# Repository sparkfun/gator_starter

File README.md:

SparkFun gator:starter Protosnap
========================================

[*SparkFun gator:starter - SEN-14891*](https://www.sparkfun.com/products/14891)

The gator:starter breaks out a temperature sensor, light sensor, and RGB LED into an alligator clippable format for use with micro:bit as well as the gator:bit expansion for micro:bit.

Repository Contents
-------------------

* **/Firmware** - Example code used with the gator:starter. While they are compiled HEX codes, you can modify the example code once they are imported into MakeCode editor.
* **/Hardware** - Eagle design files (.brd, .sch)
* **/Production** - Production panel files (.brd)

Documentation
--------------
* **[Library](https://github.com/sparkfun/pxt-gator-temp) - PXT temperature sensor firmware
* **[Hookup Guide](https://learn.sparkfun.com/tutorials/gatorstarter-protosnap-hookup-guide)** - Basic hookup guide for the gator:starter.

Product Versions
----------------
* [SEN-14891](https://www.sparkfun.com/products/14891)- The gator:starter contains a few gator-clippable sensors (Temperature and Light) along with an RGB LED

License Information
-------------------

This product is _**open source**_! 

Please review the LICENSE.md file for license information. 

If you have any questions or concerns on licensing, please contact techsupport@sparkfun.com.

Distributed as-is; no warranty is given.

- Your friends at SparkFun.

_<COLLABORATION CREDIT>_

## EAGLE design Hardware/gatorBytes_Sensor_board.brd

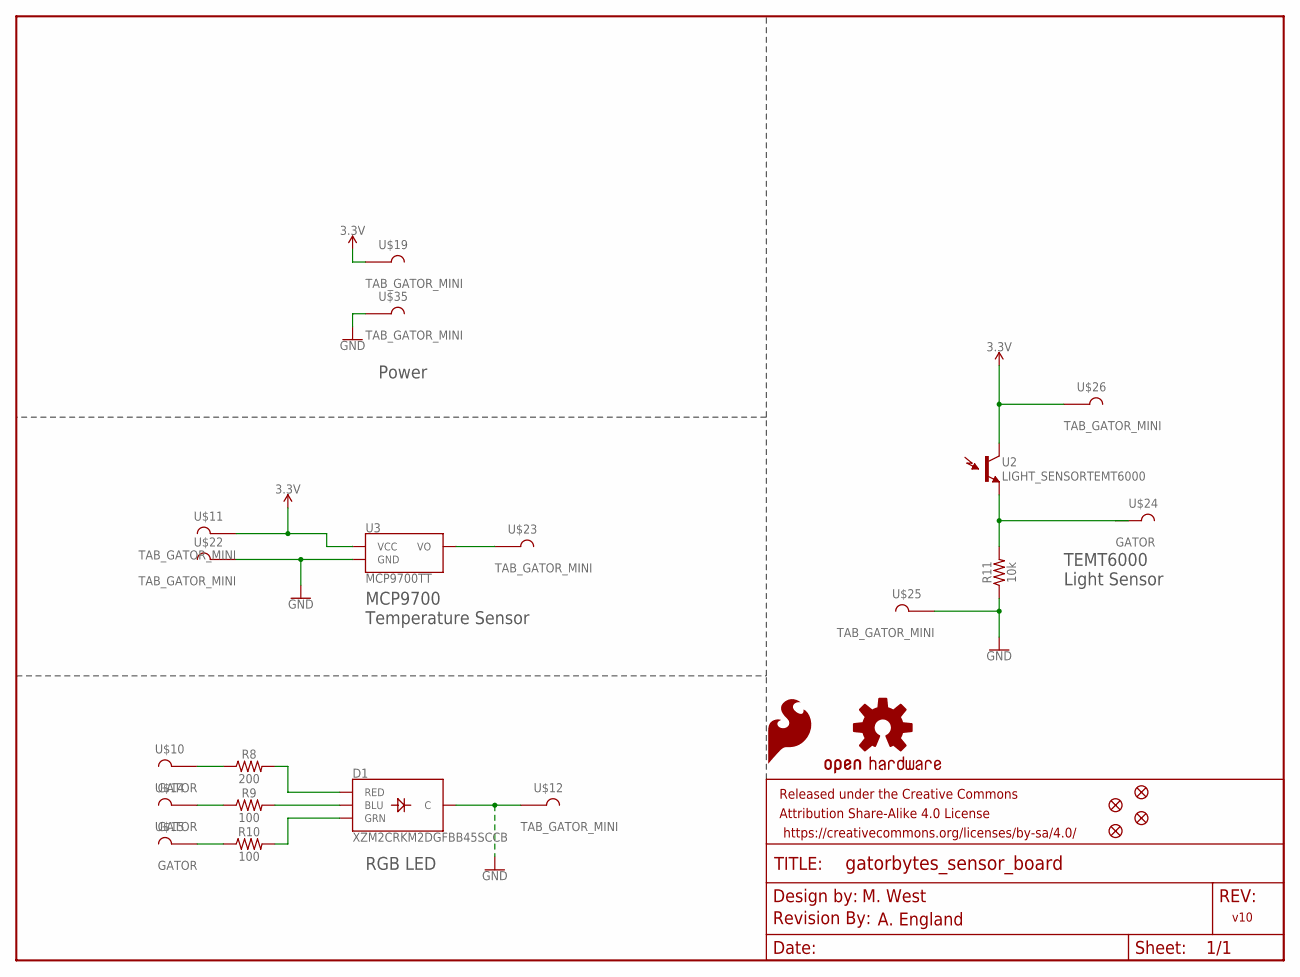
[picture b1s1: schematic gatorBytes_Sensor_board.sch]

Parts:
D1: XZM2CRKM2DGFBB45SCCB; PLCC4SMDLED
FD1, FD2, FD3, FD4: FIDUCIALUFIDUCIAL; FIDUCIAL-MICRO
FRAME1: FRAME-LETTER; CREATIVE_COMMONS
LOGO1: SFE_LOGO_FLAME.1_INCH; SFE_LOGO_FLAME_.1
LOGO2: OSHW-LOGOS; OSHW-LOGO-S
LOGO7: REVISION
R8: 200; 0603
R9, R10: 100; 0603
R11: 10k; 0603
U2: LIGHT_SENSORTEMT6000; TEMT6000
U3: MCP9700TT; SOT23-3
U$10, U$14, U$15, U$24: GATOR
U$11, U$12, U$19, U$22, U$23, U$25, U$26, U$35: TAB_GATOR_MINI

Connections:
3.3V: U2.COLLECTOR (C1), U3.1 (VCC), U$11.P1, U$19.P1, U$26.P1
GND: D1.4 (C), R11.1, U3.3 (GND), U$12.P1, U$22.P1, U$25.P1, U$35.P1
unnamed: U3.2 (VO), U$23.P1
unnamed: D1.3 (BLU), R9.2
unnamed: D1.1 (RED), R8.2
unnamed: D1.2 (GRN), R10.2
unnamed: R8.1, U$10.P$1, U$10.P$2
unnamed: R9.1, U$14.P$1, U$14.P$2
unnamed: R10.1, U$15.P$1, U$15.P$2
unnamed: R11.2, U2.EMITTER (E1), U$24.P$1, U$24.P$2

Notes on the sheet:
RGB LED
MCP9700 Temperature Sensor
TEMT6000 Light Sensor
M. West
v10
Power
A. England

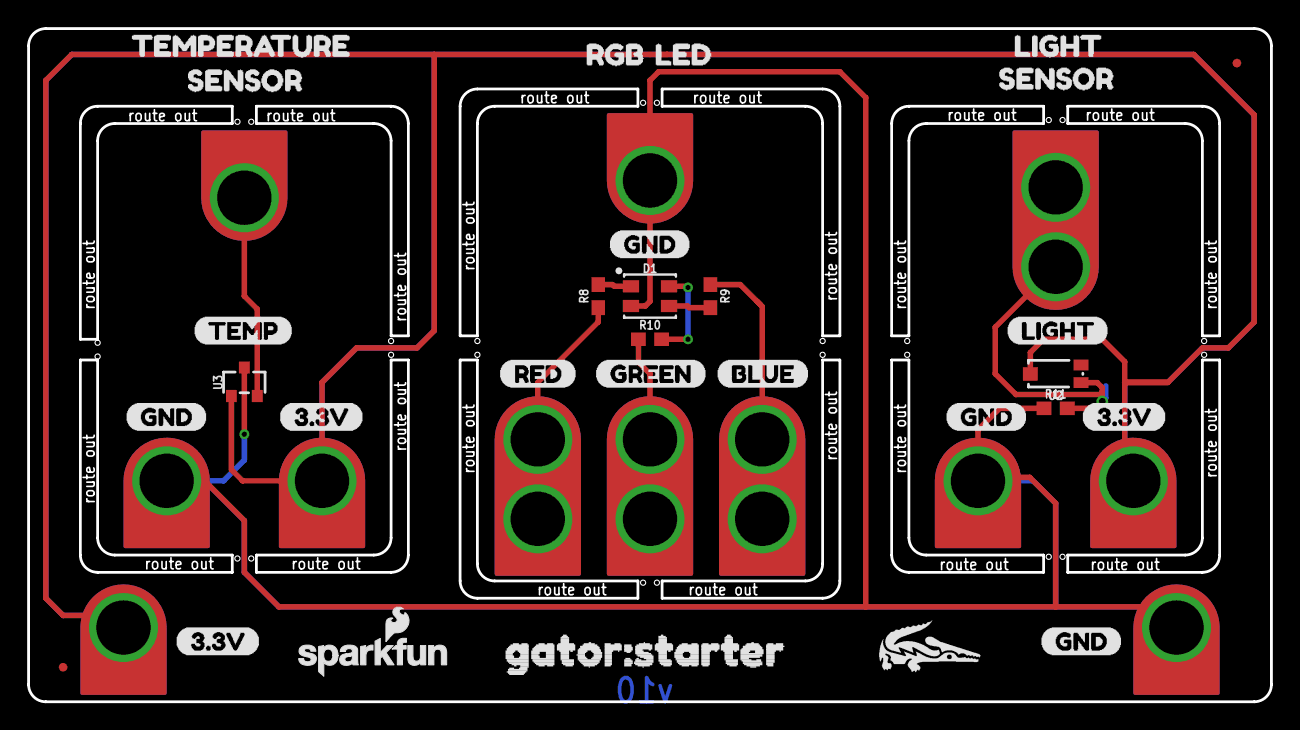
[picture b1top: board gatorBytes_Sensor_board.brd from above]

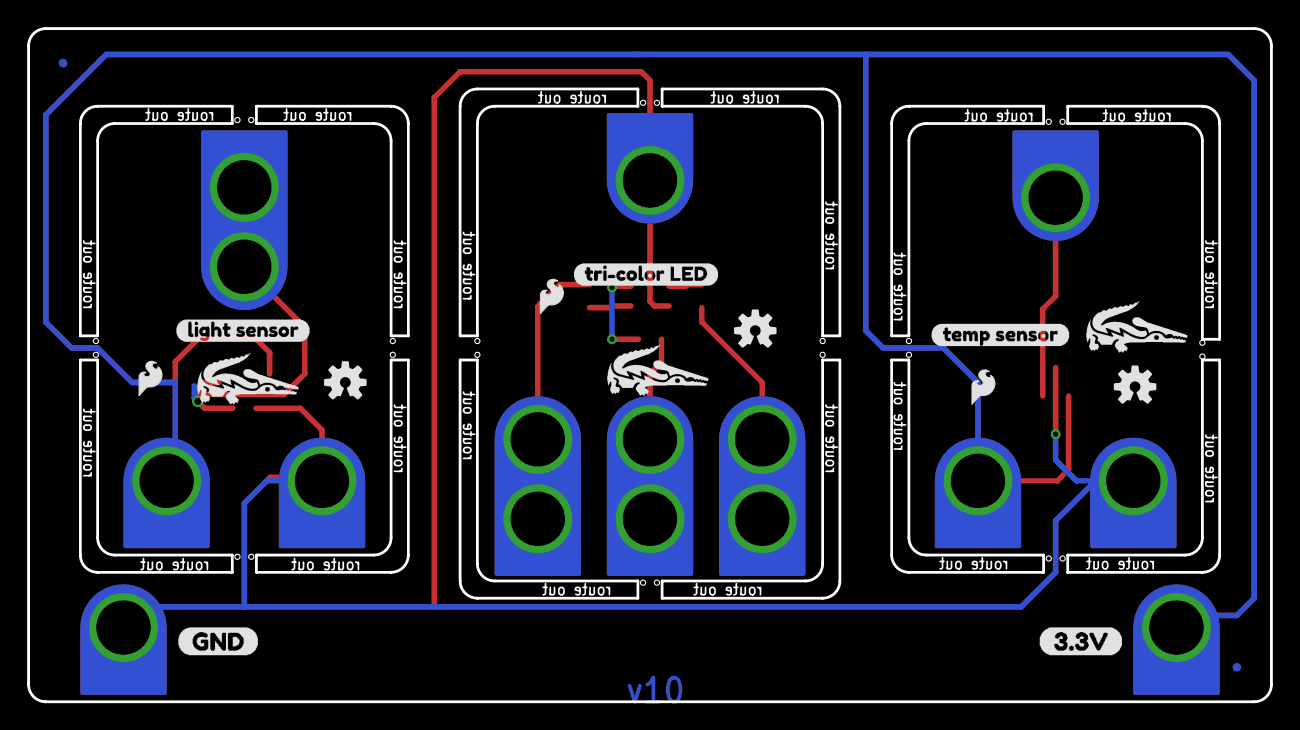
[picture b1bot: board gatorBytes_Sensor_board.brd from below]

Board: 2 copper layers, 91.4 x 49.5 mm, 61 parts (16 on the bottom side), 10 nets.

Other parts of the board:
LOGO3, LOGO5: OSHW-LOGOS; OSHW-LOGO-S
LOGO4, LOGO6: SFE_LOGO_FLAME.1_INCH; SFE_LOGO_FLAME_.1
U$1, U$6, U$7, U$38, U$39: GND0
U$2, U$3, U$36, U$37: 3#3V1
U$4: BLUE10
U$5: SFE_LOGO_NAME_FLAME_.1
U$8: GREEN9
U$9, U$20: LIGHT4
U$13: TEMP3
U$16, U$21: SENSOR2
U$17: TEMPERATURE3
U$18: RED8
U$27: LED5
U$28, U$29, U$41, U$70: GATOR#PNG
U$30: GATOR#STARTER0
U$31: LIGHT_SENSOR0
U$32: TEMP_SENSOR3
U$33: ORDERING_INSTRUCTIONS
U$34: TRI#COLOR_LED1
U$40: RGB0

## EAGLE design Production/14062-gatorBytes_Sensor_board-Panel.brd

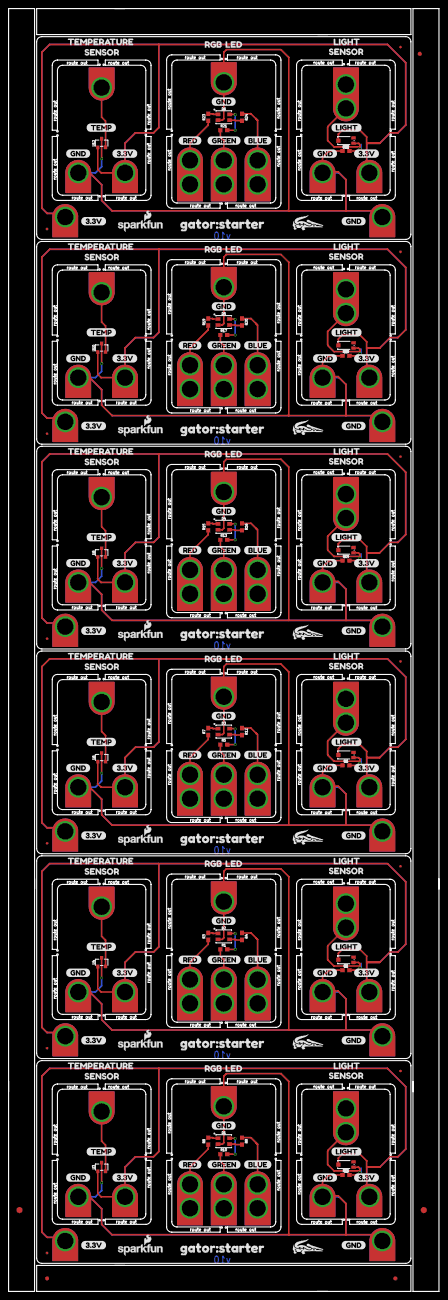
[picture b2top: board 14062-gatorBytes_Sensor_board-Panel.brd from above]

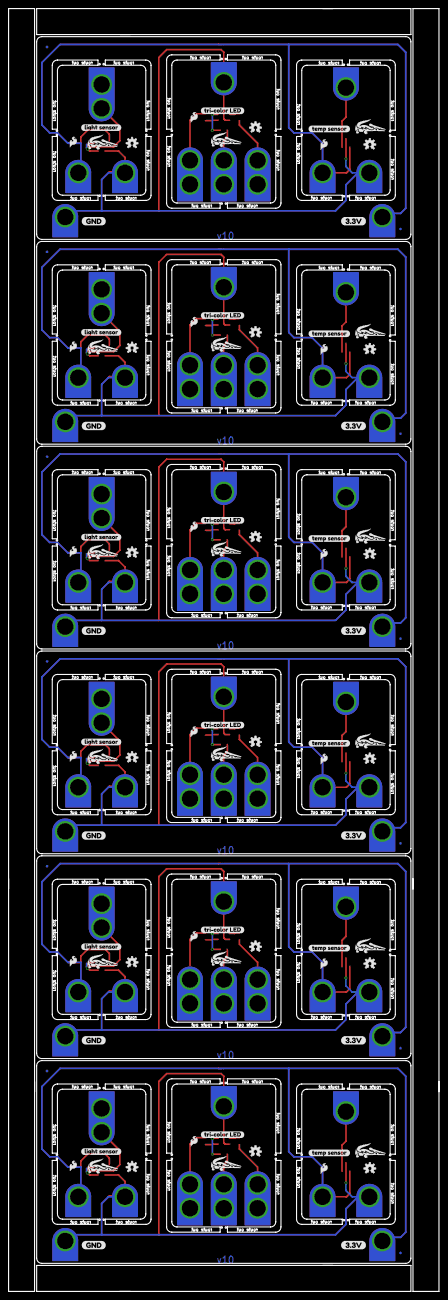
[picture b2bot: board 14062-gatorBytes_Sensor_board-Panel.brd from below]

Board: 2 copper layers, 105.2 x 313.4 mm, 353 parts (96 on the bottom side), 60 nets.

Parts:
D1, D2, D3, D4, D5, D6: XZM2CRKM2DGFBB45SCCB; PLCC4SMDLED
E$1, E$5, E$6: FIDUCIAL-1X2
E$3, E$4: FIDUCIAL-1.5X3
FD1, FD2, FD3, FD4, FD5, FD6, FD7, FD8, FD9, FD10, FD11, FD12, FD13, FD14, FD15, FD16, FD17, FD18, FD19, FD20, FD21, FD22, FD23, FD24: FIDUCIALUFIDUCIAL; FIDUCIAL-MICRO
LOGO1, LOGO4, LOGO6, LOGO7, LOGO10, LOGO12, LOGO13, LOGO16, LOGO18, LOGO19, LOGO22, LOGO24, LOGO25, LOGO28, LOGO30, LOGO31, LOGO34, LOGO36: SFE_LOGO_FLAME.1_INCH; SFE_LOGO_FLAME_.1
LOGO2, LOGO3, LOGO5, LOGO8, LOGO9, LOGO11, LOGO14, LOGO15, LOGO17, LOGO20, LOGO21, LOGO23, LOGO26, LOGO27, LOGO29, LOGO32, LOGO33, LOGO35: OSHW-LOGOS; OSHW-LOGO-S
R1, R4, R5, R9, R10, R12, R13, R16, R17, R20, R21, R24: 100; 0603
R2, R6, R11, R14, R18, R22: 10k; 0603
R3, R7, R8, R15, R19, R23: 200; 0603
U1, U2, U5, U7, U9, U11: LIGHT_SENSORTEMT6000; TEMT6000
U3, U4, U6, U8, U10, U12: MCP9700TT; SOT23-3
U$1, U$6, U$7, U$38, U$39, U$54, U$55, U$77, U$78, U$82, U$96, U$97, U$118, U$119, U$123, U$137, U$138, U$159, U$160, U$164, U$178, U$179, U$200, U$201, U$205, U$219, U$220, U$241, U$242, U$246: GND0
U$2, U$3, U$36, U$37, U$51, U$52, U$75, U$76, U$93, U$94, U$116, U$117, U$134, U$135, U$157, U$158, U$175, U$176, U$198, U$199, U$216, U$217, U$239, U$240: 3#3V1
U$4, U$53, U$95, U$136, U$177, U$218: BLUE10
U$5, U$72, U$113, U$154, U$195, U$236: SFE_LOGO_NAME_FLAME_.1
U$8, U$56, U$98, U$139, U$180, U$221: GREEN9
U$9, U$20, U$57, U$62, U$99, U$104, U$140, U$145, U$181, U$186, U$222, U$227: LIGHT4
U$10, U$14, U$15, U$24, U$33, U$44, U$45, U$48, U$83, U$86, U$87, U$90, U$124, U$127, U$128, U$131, U$165, U$168, U$169, U$172, U$206, U$209, U$210, U$213: GATOR
U$11, U$12, U$19, U$22, U$23, U$25, U$26, U$35, U$42, U$43, U$46, U$47, U$49, U$50, U$73, U$74, U$84, U$85, U$88, U$89, U$91, U$92, U$114, U$115, U$125, U$126, U$129, U$130, U$132, U$133, U$155, U$156, U$166, U$167, U$170, U$171, U$173, U$174, U$196, U$197, U$207, U$208, U$211, U$212, U$214, U$215, U$237, U$238: TAB_GATOR_MINI
U$13, U$58, U$100, U$141, U$182, U$223: TEMP3
U$16, U$21, U$61, U$63, U$103, U$105, U$144, U$146, U$185, U$187, U$226, U$228: SENSOR2
U$17, U$60, U$102, U$143, U$184, U$225: TEMPERATURE3
U$18, U$59, U$101, U$142, U$183, U$224: RED8
U$27, U$64, U$106, U$147, U$188, U$229: LED5
U$28, U$29, U$41, U$65, U$66, U$67, U$70, U$80, U$107, U$108, U$109, U$121, U$148, U$149, U$150, U$162, U$189, U$190, U$191, U$203, U$230, U$231, U$232, U$244: GATOR#PNG
U$30, U$81, U$122, U$163, U$204, U$245: GATOR#STARTER0
U$31, U$68, U$110, U$151, U$192, U$233: LIGHT_SENSOR0
U$32, U$69, U$111, U$152, U$193, U$234: TEMP_SENSOR3
U$34, U$71, U$112, U$153, U$194, U$235: TRI#COLOR_LED1
U$40, U$79, U$120, U$161, U$202, U$243: RGB0

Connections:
3.3V: U2.COLLECTOR, U3.1, U$11.P1, U$19.P1, U$26.P1
3.3V1: U1.COLLECTOR, U4.1, U$42.P1, U$50.P1, U$73.P1
3.3V2: U5.COLLECTOR, U6.1, U$84.P1, U$92.P1, U$114.P1
3.3V3: U7.COLLECTOR, U8.1, U$125.P1, U$133.P1, U$155.P1
3.3V4: U9.COLLECTOR, U10.1, U$166.P1, U$174.P1, U$196.P1
3.3V5: U11.COLLECTOR, U12.1, U$207.P1, U$215.P1, U$237.P1
GND: D1.4, R11.1, U3.3, U$12.P1, U$22.P1, U$25.P1, U$35.P1
GND1: D2.4, R2.1, U4.3, U$43.P1, U$46.P1, U$49.P1, U$74.P1
GND2: D3.4, R6.1, U6.3, U$85.P1, U$88.P1, U$91.P1, U$115.P1
GND3: D4.4, R14.1, U8.3, U$126.P1, U$129.P1, U$132.P1, U$156.P1
GND4: D5.4, R18.1, U10.3, U$167.P1, U$170.P1, U$173.P1, U$197.P1
GND5: D6.4, R22.1, U12.3, U$208.P1, U$211.P1, U$214.P1, U$238.P1
unnamed: D2.3, R4.2
unnamed: D2.1, R3.2
unnamed: D2.2, R1.2
unnamed: R3.1, U$33.P$1, U$33.P$2
unnamed: R4.1, U$44.P$1, U$44.P$2
unnamed: R1.1, U$45.P$1, U$45.P$2
unnamed: U4.2, U$47.P1
unnamed: R2.2, U1.EMITTER, U$48.P$1, U$48.P$2
unnamed: D3.3, R12.2
unnamed: U3.2, U$23.P1
unnamed: D1.3, R9.2
unnamed: D1.1, R8.2
unnamed: D1.2, R10.2
unnamed: R8.1, U$10.P$1, U$10.P$2
unnamed: R9.1, U$14.P$1, U$14.P$2
unnamed: R10.1, U$15.P$1, U$15.P$2
unnamed: D3.1, R7.2
unnamed: R11.2, U2.EMITTER, U$24.P$1, U$24.P$2
unnamed: D3.2, R5.2
unnamed: R7.1, U$83.P$1, U$83.P$2
unnamed: R12.1, U$86.P$1, U$86.P$2
unnamed: R5.1, U$87.P$1, U$87.P$2
unnamed: U6.2, U$89.P1
unnamed: R6.2, U5.EMITTER, U$90.P$1, U$90.P$2
unnamed: D4.3, R16.2
unnamed: D4.1, R15.2
unnamed: D4.2, R13.2
unnamed: R15.1, U$124.P$1, U$124.P$2
unnamed: R16.1, U$127.P$1, U$127.P$2
unnamed: R13.1, U$128.P$1, U$128.P$2
unnamed: U8.2, U$130.P1
unnamed: R14.2, U7.EMITTER, U$131.P$1, U$131.P$2
unnamed: D5.3, R20.2
unnamed: D5.1, R19.2
unnamed: D5.2, R17.2
unnamed: R19.1, U$165.P$1, U$165.P$2
unnamed: R20.1, U$168.P$1, U$168.P$2
unnamed: R17.1, U$169.P$1, U$169.P$2
unnamed: U10.2, U$171.P1
unnamed: R18.2, U9.EMITTER, U$172.P$1, U$172.P$2
unnamed: D6.3, R24.2
unnamed: D6.1, R23.2
unnamed: D6.2, R21.2
unnamed: R23.1, U$206.P$1, U$206.P$2
unnamed: R24.1, U$209.P$1, U$209.P$2
unnamed: R21.1, U$210.P$1, U$210.P$2
unnamed: U12.2, U$212.P1
unnamed: R22.2, U11.EMITTER, U$213.P$1, U$213.P$2

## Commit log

2018-08-23 removing pth
2018-09-12 adding new tabs
2018-09-12 pre reds changes
2018-09-12 post design review changes
2018-09-12 post checklist chanegs
2018-09-13 post qc checklist
2018-09-14 created panel v10
2018-10-16 silk update
2018-10-16 panel
2018-10-18 cleaning repo, updating readme
2018-10-18 fix small readme issue
2018-10-18 updating readme
2019-01-09 gator:starter Example Code HEX files
    Add compiled MakeCode example code used with gator:starter

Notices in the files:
parts and their libraries:
SparkFun-LED: Licensing: Creative Commons ShareAlike 4.0 International - https://creativecommons.org/licenses/by-sa/4.0
SparkFun-Aesthetics: Released under the Creative Commons Attribution Share-Alike 4.0 License
SparkFun-Aesthetics: https://creativecommons.org/licenses/by-sa/4.0
